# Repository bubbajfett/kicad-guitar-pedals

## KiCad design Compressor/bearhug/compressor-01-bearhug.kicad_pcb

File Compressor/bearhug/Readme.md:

# Bearhug

Guitar Pedal PCB based on Bearhug compressor.

Edit --- found a bug, and am now re-verifying this.   Consider this unverified, though it passes sound ok.

All registered trademarks are owned by their respective owners.

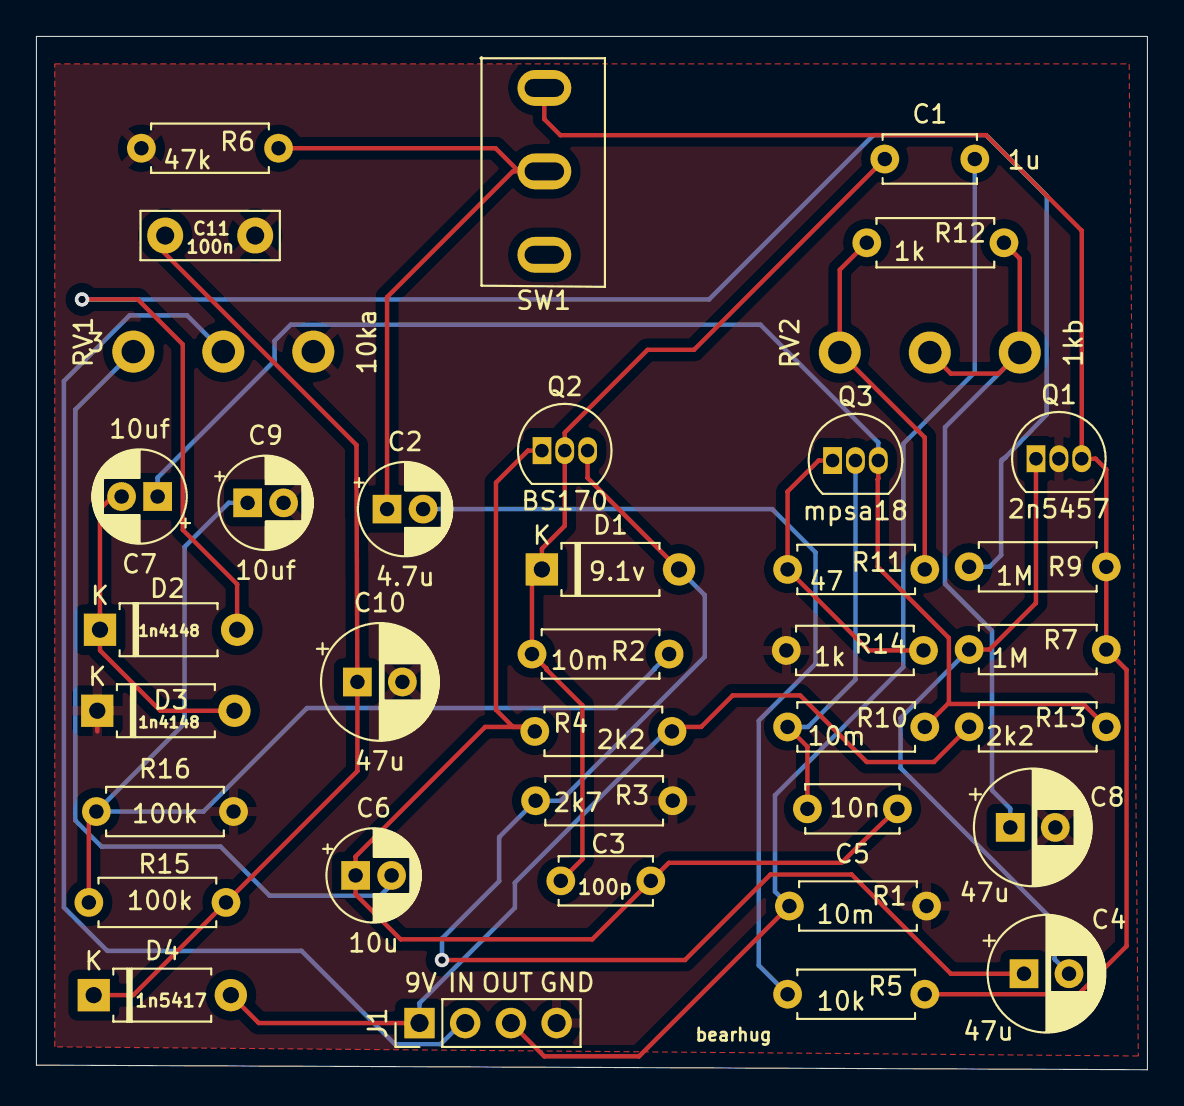
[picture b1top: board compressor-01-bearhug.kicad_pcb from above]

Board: 2 copper layers, 61.7 x 57.4 mm, 37 parts (0 on the bottom side), 21 nets.

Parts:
C1: 1u; C_Disc_D5.0mm_W2.5mm_P5.00mm
C2: 4.7u; CP_Radial_D5.0mm_P2.00mm
C3: 100p; C_Disc_D5.0mm_W2.5mm_P5.00mm
C4, C8, C10: 47u; CP_Radial_D6.3mm_P2.50mm
C5: 10n; C_Disc_D5.0mm_W2.5mm_P5.00mm
C6: 10u; CP_Radial_D5.0mm_P2.00mm
C7, C9: 10uf; CP_Radial_D5.0mm_P2.00mm
C11: 100n; C_Disc_D7.5mm_W2.5mm_P5.00mm
D1: 9.1v; D_A-405_P7.62mm_Horizontal
D2, D3: 1n4148; D_A-405_P7.62mm_Horizontal
D4: 1n5417; D_A-405_P7.62mm_Horizontal
J1: Conn_01x05; PinHeader_1x04_P2.54mm_Vertical
Q1: 2n5457; TO-92_Inline
Q2: BS170; TO-92_Inline
Q3: mpsa18; TO-92_Inline
R1, R2, R10: 10m; R_Axial_DIN0207_L6.3mm_D2.5mm_P7.62mm_Horizontal
R3: 2k7; R_Axial_DIN0207_L6.3mm_D2.5mm_P7.62mm_Horizontal
R4, R13: 2k2; R_Axial_DIN0207_L6.3mm_D2.5mm_P7.62mm_Horizontal
R5: 10k; R_Axial_DIN0207_L6.3mm_D2.5mm_P7.62mm_Horizontal
R6: 47k; R_Axial_DIN0207_L6.3mm_D2.5mm_P7.62mm_Horizontal
R7, R9: 1M; R_Axial_DIN0207_L6.3mm_D2.5mm_P7.62mm_Horizontal
R11: 47; R_Axial_DIN0207_L6.3mm_D2.5mm_P7.62mm_Horizontal
R12, R14: 1k; R_Axial_DIN0207_L6.3mm_D2.5mm_P7.62mm_Horizontal
R15, R16: 100k; R_Axial_DIN0207_L6.3mm_D2.5mm_P7.62mm_Horizontal
RV1: 10ka; Pot_Underside
RV2: 1kb; Pot_Underside
SW1: SW_SPST; SWITCH-M1-SPDT

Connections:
9v: D4.2 (A), J1.1, R4.1, R13.1
GND: C8.2, C9.2, C10.2, C11.2, D3.1 (K), J1.4, Q1.2 (S), R1.2, R3.2, R6.1, R14.2, R16.2, RV1.1
IN: C1.2, J1.3, R1.1
unnamed: C2.2, R5.1
unnamed: C6.2, RV1.3
unnamed: C8.1, R12.2, RV2.1, RV2.2
unnamed: C4.1, D1.2 (A), Q2.3 (S), R3.1
unnamed: C1.1, C3.1, D1.1 (K), Q2.2 (G), R2.1
unnamed: D2.2 (A), R9.2
unnamed: C7.2, D2.1 (K), D3.2 (A)
unnamed: C10.1, C11.1, D4.1 (K), R15.1
unnamed: C4.2, Q1.1 (D), R7.1
unnamed: Q1.3 (G), R5.2, R7.2, R9.1, SW1.1 (A)
unnamed: C3.2, C5.1, C6.1, Q2.1 (D), R4.2
unnamed: C5.2, Q3.2 (B), R10.1
unnamed: C7.1, Q3.3 (C), R10.2, R13.2
unnamed: Q3.1 (E), R11.1, R14.1
unnamed: R11.2, R12.1, RV2.3
unnamed: C2.1, R6.2, SW1.2 (B)
OUT: J1.2, RV1.2
VB: C9.1, R2.2, R15.2, R16.1

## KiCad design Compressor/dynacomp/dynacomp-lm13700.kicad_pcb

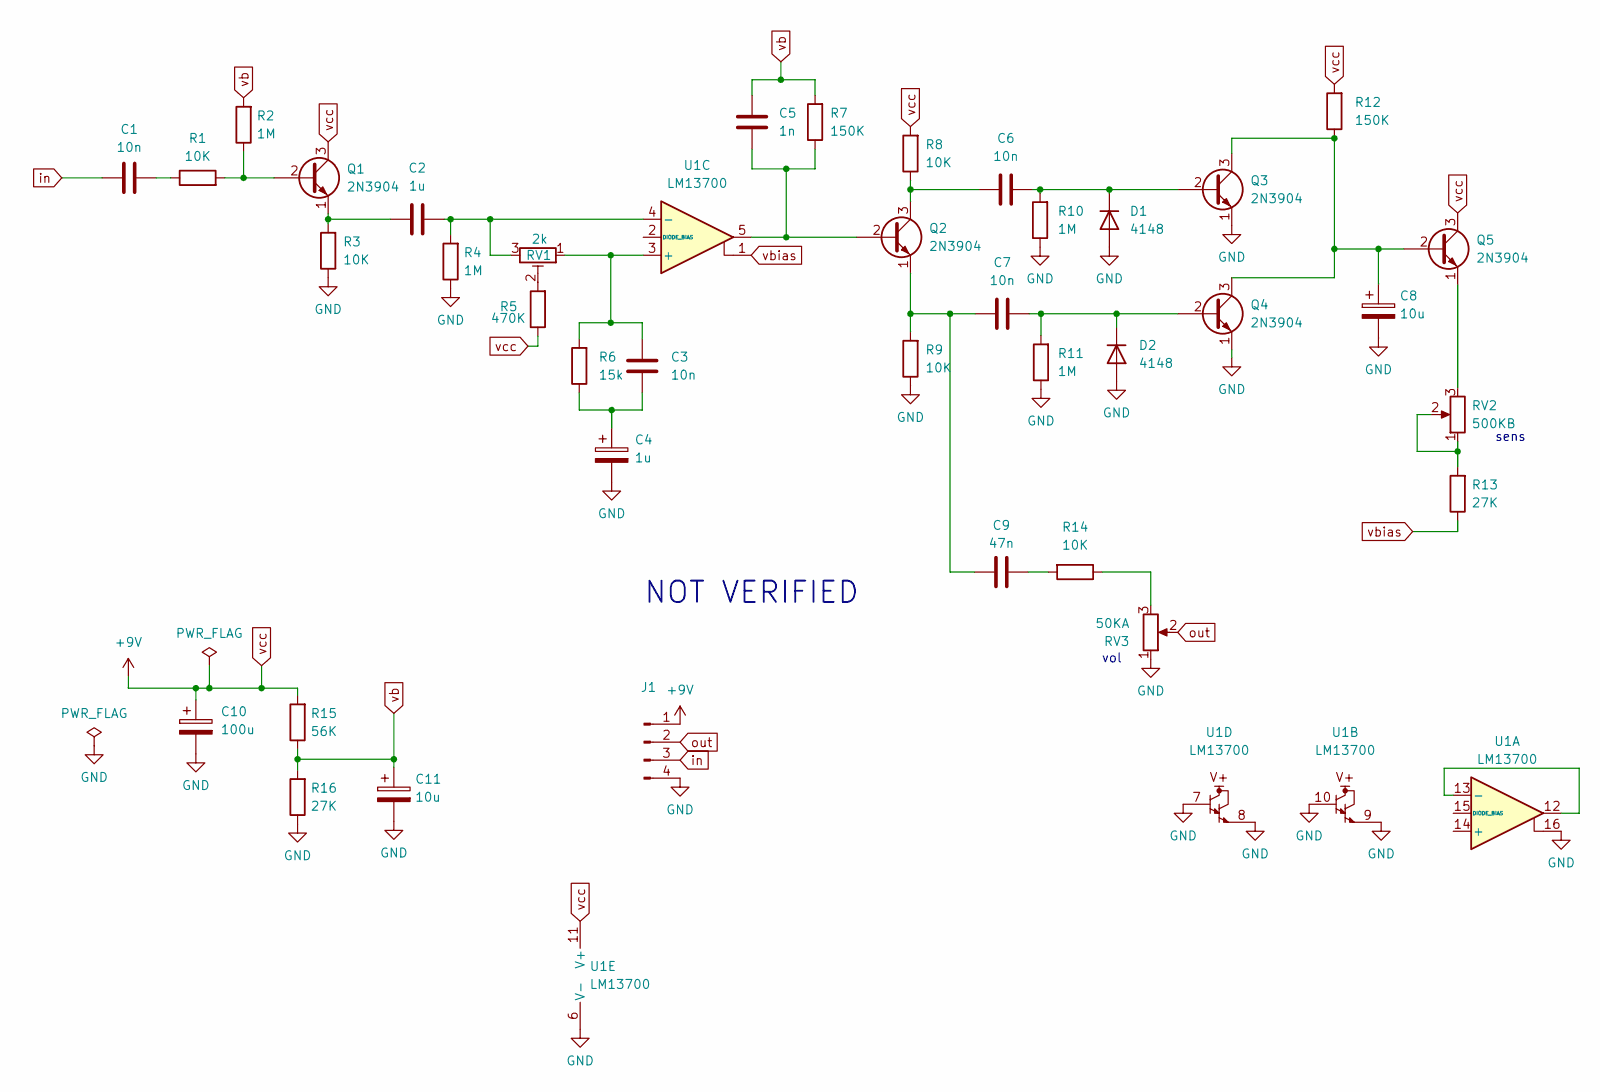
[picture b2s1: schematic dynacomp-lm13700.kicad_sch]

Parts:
C1, C3, C6, C7: 10n; C_Rect_L7.0mm_W2.0mm_P5.00mm
C2: 1u; C_Rect_L7.0mm_W3.5mm_P5.00mm
C4: 1u; CP_Radial_D5.0mm_P2.00mm
C5: 1n; C_Rect_L7.0mm_W2.0mm_P5.00mm
C8, C11: 10u; CP_Radial_D5.0mm_P2.00mm
C9: 47n; C_Rect_L7.0mm_W2.0mm_P5.00mm
C10: 100u; CP_Radial_D6.3mm_P2.50mm
D1, D2: 4148; D_DO-35_SOD27_P7.62mm_Horizontal
J1: Conn_01x04_Pin; PinHeader_1x04_P2.54mm_Vertical
Q1, Q2, Q3, Q4, Q5: 2N3904; TO-92_Inline
R1, R3, R8, R9, R14: 10K; R_Axial_DIN0207_L6.3mm_D2.5mm_P10.16mm_Horizontal
R2, R4, R10, R11: 1M; R_Axial_DIN0207_L6.3mm_D2.5mm_P10.16mm_Horizontal
R5: 470K; R_Axial_DIN0207_L6.3mm_D2.5mm_P10.16mm_Horizontal
R6: 15k; R_Axial_DIN0207_L6.3mm_D2.5mm_P10.16mm_Horizontal
R7, R12: 150K; R_Axial_DIN0207_L6.3mm_D2.5mm_P10.16mm_Horizontal
R13, R16: 27K; R_Axial_DIN0207_L6.3mm_D2.5mm_P10.16mm_Horizontal
R15: 56K; R_Axial_DIN0207_L6.3mm_D2.5mm_P10.16mm_Horizontal
RV1: 2k; Potentiometer_Runtron_RM-065_Vertical
RV2: 500KB; Pot_Underside
RV3: 50KA; Pot_Underside
U1: LM13700; DIP-16_W7.62mm

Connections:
GND: C4.2, C8.2, C10.2, C11.2, D1.2 (A), D2.2 (A), J1.4, Q3.1 (E), Q4.1 (E), R3.1, R4.1, R9.1, R10.1, R11.1, R16.1, RV3.1, U1.6 (V-), U1.7, U1.8, U1.9, U1.10, U1.16
unnamed: C1.2, R1.1
unnamed: C3.2, C4.1, R6.1
unnamed: C9.2, R14.2
unnamed: C6.2, D1.1 (K), Q3.2 (B), R10.2
unnamed: C7.2, D2.1 (K), Q4.2 (B), R11.2
unnamed: Q1.2 (B), R1.2, R2.1
unnamed: C2.1, Q1.1 (E), R3.2
unnamed: C5.2, Q2.2 (B), R7.1, U1.5
unnamed: C6.1, Q2.3 (C), R8.1
unnamed: C7.1, C9.1, Q2.1 (E), R9.2
unnamed: C8.1, Q3.3 (C), Q4.3 (C), Q5.2 (B), R12.1
unnamed: Q5.1 (E), RV2.3
unnamed: R5.2, RV1.2
unnamed: R13.2, RV2.1, RV2.2
unnamed: R14.1, RV3.3
unnamed: U1.12, U1.13 (-)
unnamed: C3.1, R6.2, RV1.1, U1.3 (+)
unnamed: C2.2, R4.2, RV1.3, U1.4 (-)
in: C1.1, J1.3
out: J1.2, RV3.2
vb: C5.1, C11.1, R2.2, R7.2, R15.1, R16.2
vbias: R13.1, U1.1
vcc: C10.1, J1.1, Q1.3 (C), Q5.3 (C), R5.1, R8.2, R12.2, R15.2, U1.11 (V+)

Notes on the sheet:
sens
vol
NOT VERIFIED

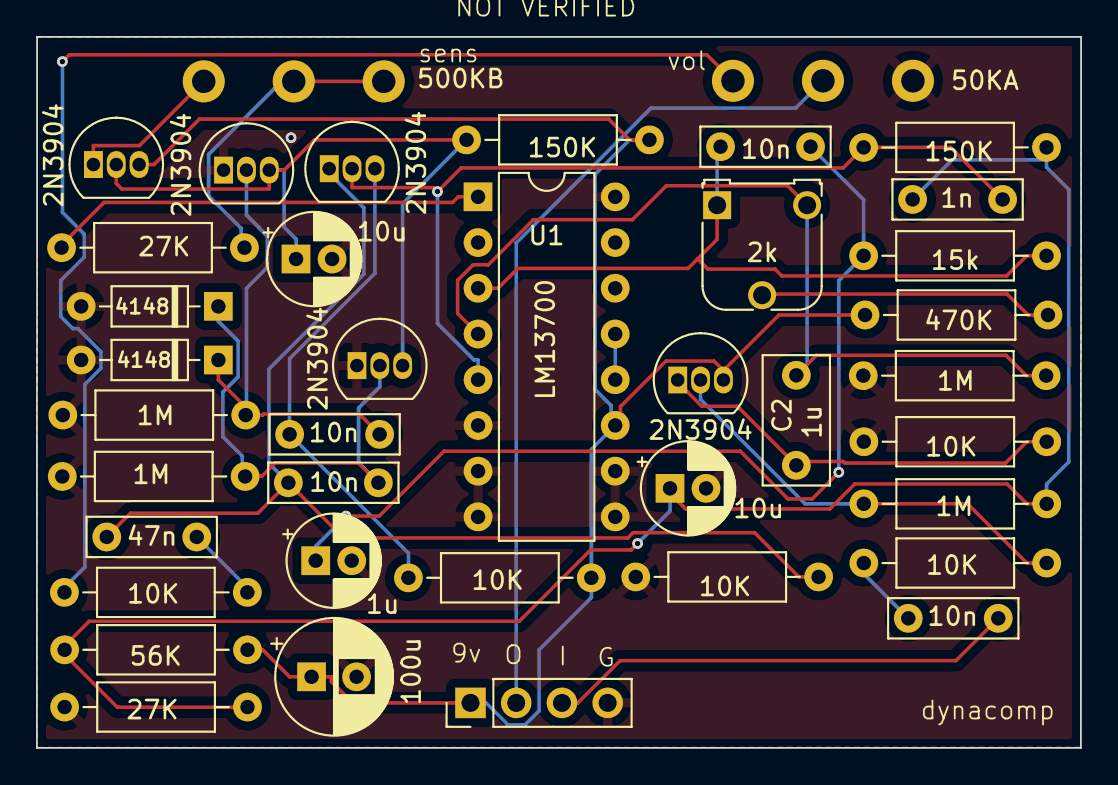
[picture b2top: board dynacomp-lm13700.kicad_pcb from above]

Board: 2 copper layers, 58.0 x 39.5 mm, 39 parts (0 on the bottom side), 24 nets.

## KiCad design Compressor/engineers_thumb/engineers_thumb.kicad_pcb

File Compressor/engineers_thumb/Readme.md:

# Engineers Thumb

This compressor uses OTA LM13700 IC for fairly subtle compression.  This
is verified.

Not sure this was a commercially sold compressor, or if it is a clone of
a commercially sold compressor.

All registered trademarks are owned by their respective owners.

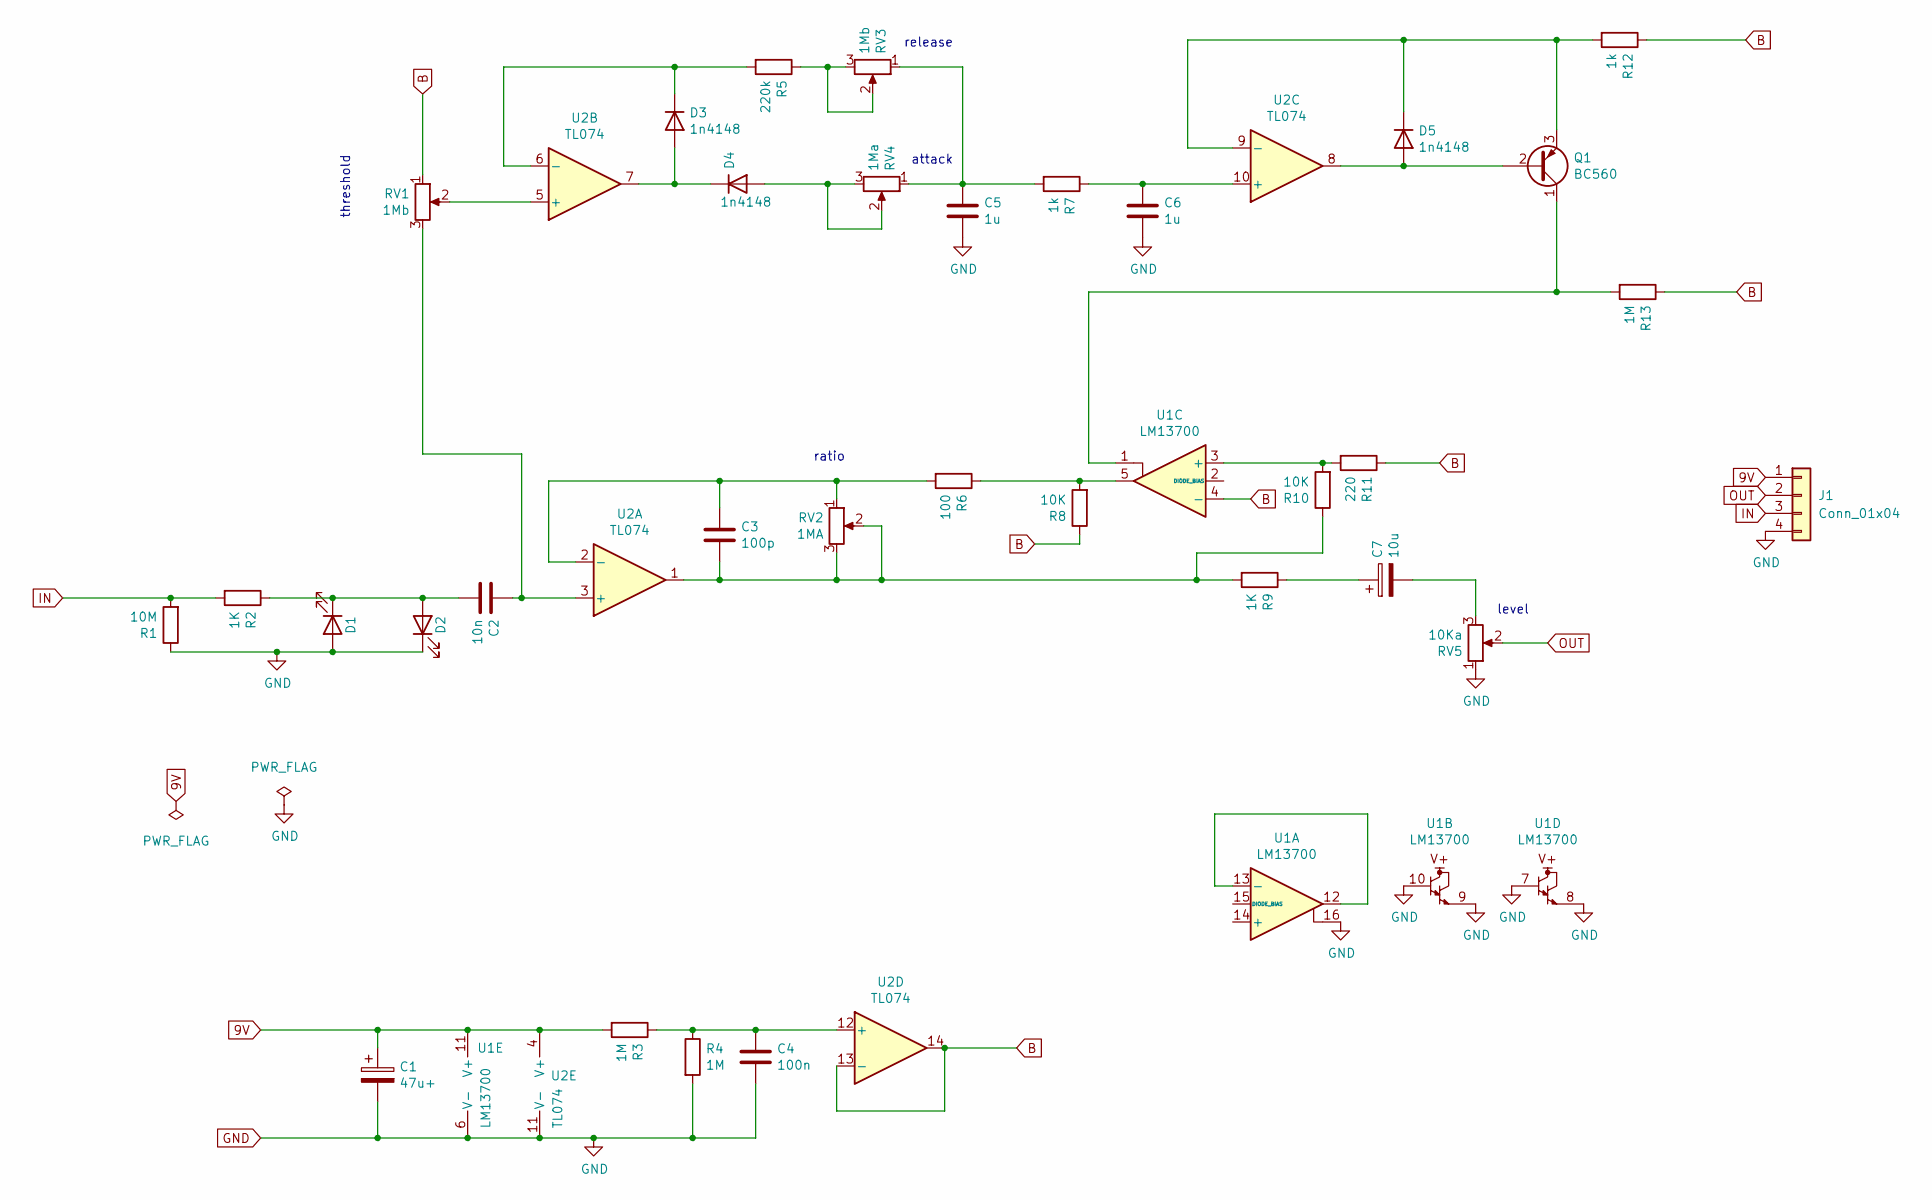
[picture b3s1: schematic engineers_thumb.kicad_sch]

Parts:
C1: 47u+; CP_Radial_D6.3mm_P2.50mm
C2: 10n; C_Rect_L7.0mm_W3.5mm_P5.00mm
C3: 100p; C_Disc_D5.1mm_W3.2mm_P5.00mm
C4: 100n; C_Rect_L7.0mm_W3.5mm_P5.00mm
C5, C6: 1u; C_Rect_L7.0mm_W3.5mm_P5.00mm
C7: 10u; CP_Radial_D5.0mm_P2.00mm
D1, D2: 3mm; LED_D3.0mm
D3, D4, D5: 1n4148; D_A-405_P7.62mm_Horizontal
J1: Conn_01x04; PinHeader_1x04_P2.54mm_Vertical
Q1: BC560; TO-92_Inline
R1: 10M; R_Axial_DIN0207_L6.3mm_D2.5mm_P10.16mm_Horizontal
R2, R9: 1K; R_Axial_DIN0207_L6.3mm_D2.5mm_P10.16mm_Horizontal
R3, R4, R13: 1M; R_Axial_DIN0207_L6.3mm_D2.5mm_P10.16mm_Horizontal
R5: 220k; R_Axial_DIN0207_L6.3mm_D2.5mm_P10.16mm_Horizontal
R6: 100; R_Axial_DIN0207_L6.3mm_D2.5mm_P10.16mm_Horizontal
R7, R12: 1k; R_Axial_DIN0207_L6.3mm_D2.5mm_P10.16mm_Horizontal
R8, R10: 10K; R_Axial_DIN0207_L6.3mm_D2.5mm_P10.16mm_Horizontal
R11: 220; R_Axial_DIN0207_L6.3mm_D2.5mm_P10.16mm_Horizontal
RV1, RV3: 1Mb; Potentiometer_Alps_RK09K_Single_Vertical
RV2: 1MA; Potentiometer_Alps_RK09K_Single_Vertical
RV4: 1Ma; Potentiometer_Alps_RK09K_Single_Vertical
RV5: 10Ka; Potentiometer_Alps_RK09K_Single_Vertical
U1: LM13700; DIP-16_W7.62mm_LongPads
U2: TL074; DIP-14_W7.62mm_LongPads

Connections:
9V: C1.1, J1.1, R3.2, U1.11 (V+), U2.4 (V+)
B: R8.1, R11.1, R12.1, R13.1, RV1.1, U1.4 (-), U2.13 (-), U2.14
GND: C1.2, C4.2, C5.2, C6.2, D1.2 (A), D2.1 (K), J1.4, R1.1, R4.2, RV5.1, U1.6 (V-), U1.7, U1.8, U1.9, U1.10, U1.16, U2.11 (V-)
IN: J1.3, R1.2, R2.2
unnamed: C3.2, R9.2, R10.1, RV2.2, RV2.3, U2.1
unnamed: C5.1, R7.2, RV3.1, RV4.1
unnamed: C7.1, R9.1
unnamed: C7.2, RV5.3
unnamed: C2.2, D1.1 (K), D2.2 (A), R2.1
unnamed: D3.2 (A), D4.1 (K), U2.7
unnamed: D3.1 (K), R5.2, U2.6 (-)
unnamed: D4.2 (A), RV4.2, RV4.3
unnamed: D5.2 (A), Q1.2 (B), U2.8
unnamed: D5.1 (K), Q1.3 (E), R12.2, U2.9 (-)
unnamed: Q1.1 (C), R13.2, U1.1
unnamed: R5.1, RV3.2, RV3.3
unnamed: R6.1, R8.2, U1.5
unnamed: U1.12, U1.13 (-)
unnamed: R10.2, R11.2, U1.3 (+)
unnamed: C2.1, RV1.3, U2.3 (+)
unnamed: C3.1, R6.2, RV2.1, U2.2 (-)
unnamed: RV1.2, U2.5 (+)
unnamed: C6.1, R7.1, U2.10 (+)
unnamed: C4.1, R3.1, R4.1, U2.12 (+)
OUT: J1.2, RV5.2

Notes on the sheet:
attack
ratio
level
threshold
release

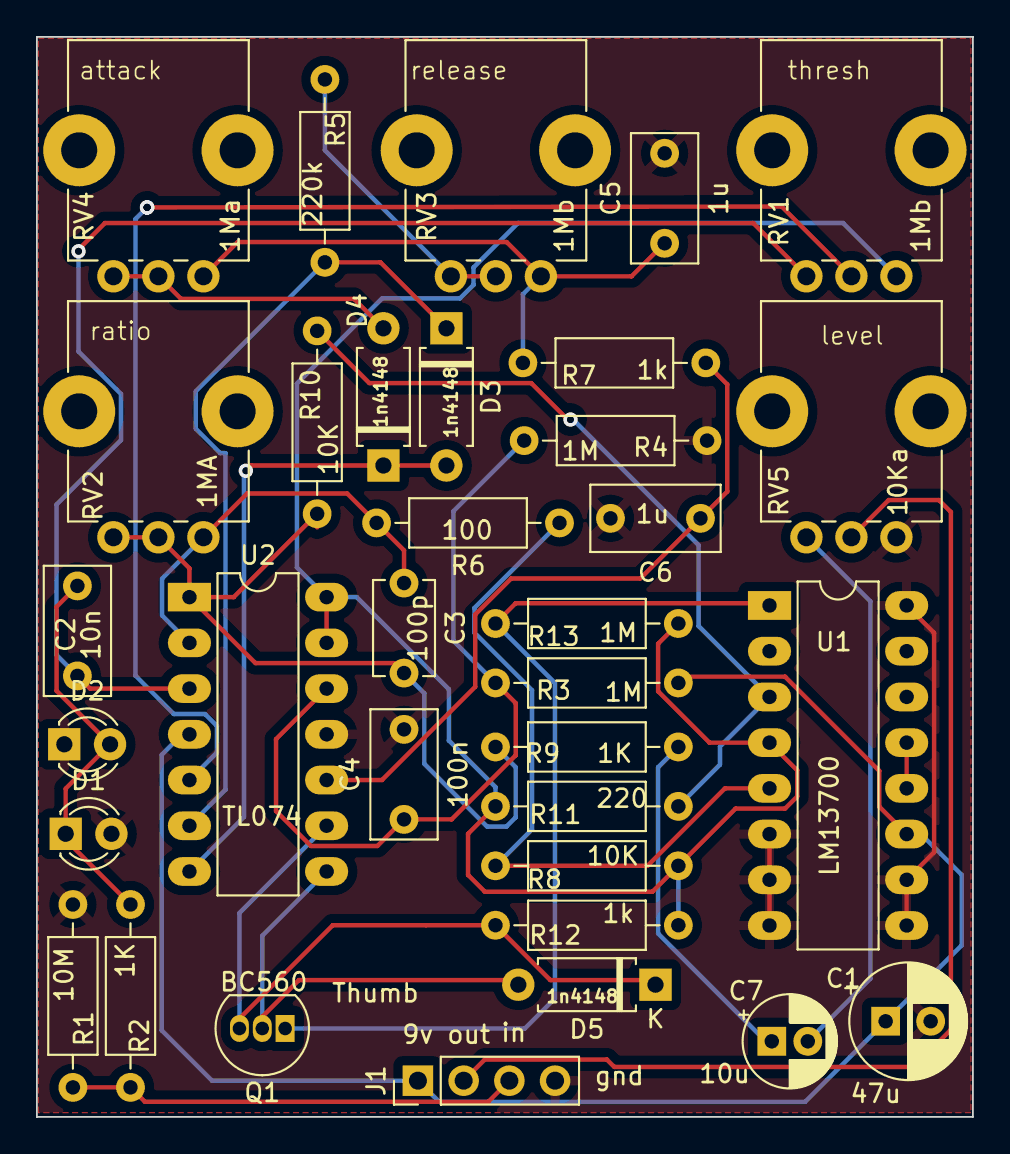
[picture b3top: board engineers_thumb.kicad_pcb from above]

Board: 2 copper layers, 52.0 x 60.0 mm, 34 parts (0 on the bottom side), 25 nets.

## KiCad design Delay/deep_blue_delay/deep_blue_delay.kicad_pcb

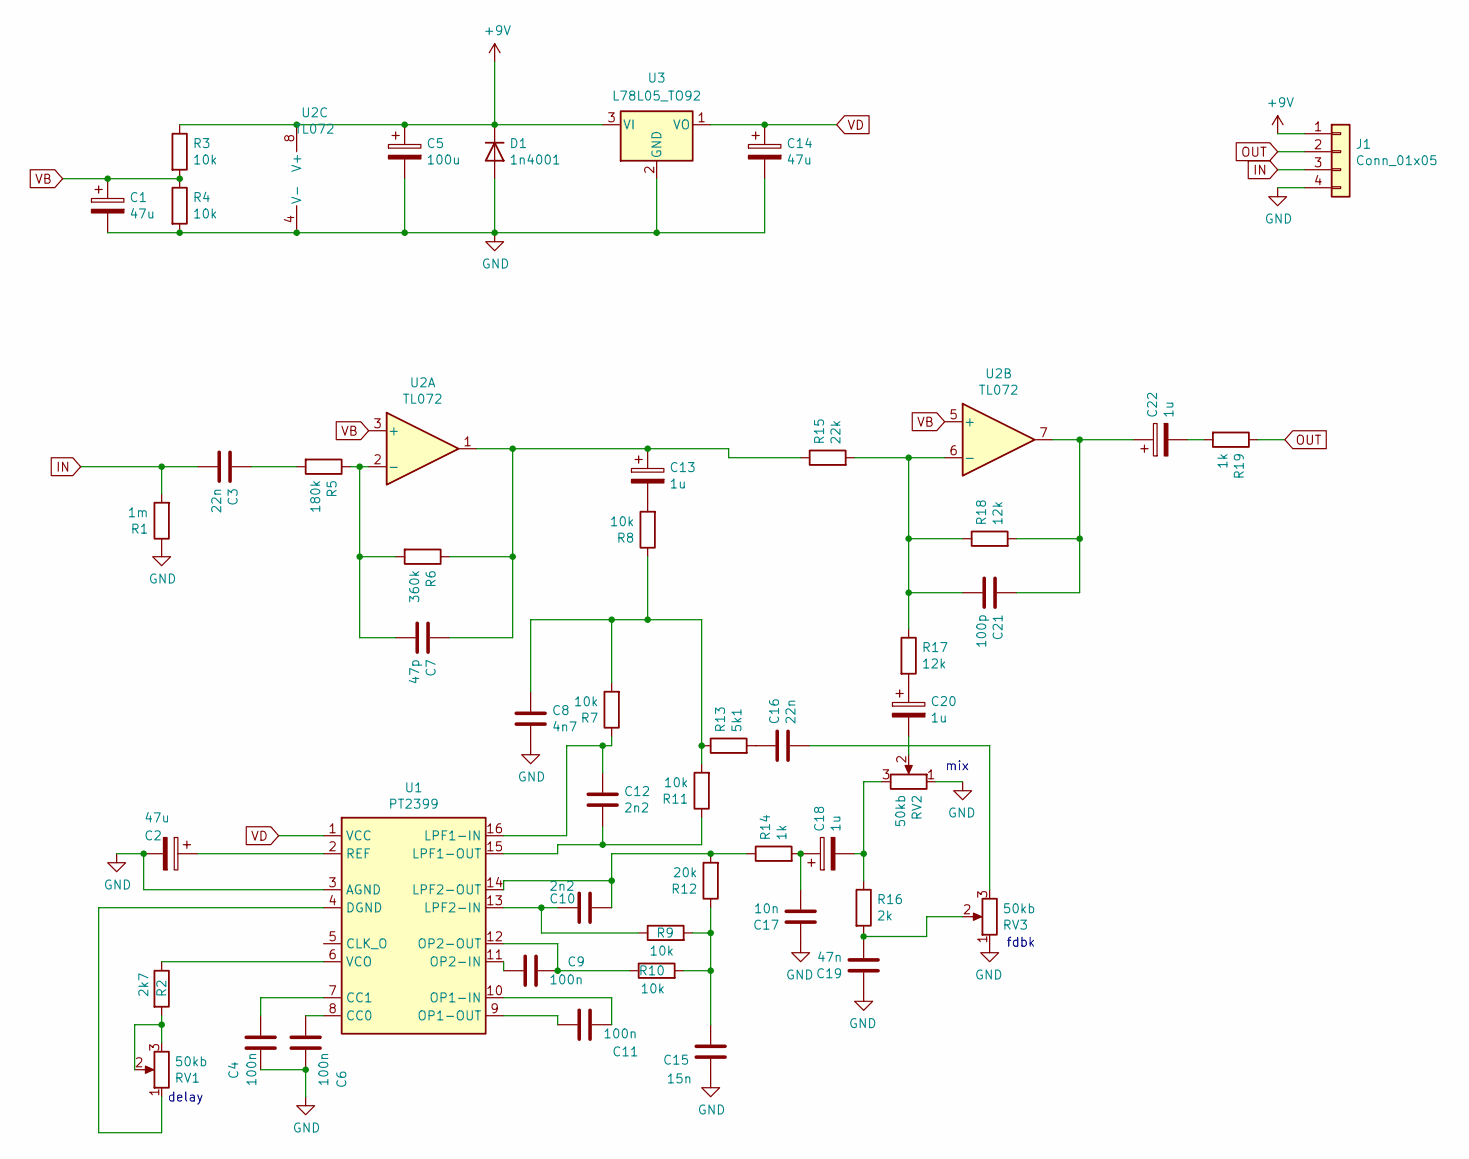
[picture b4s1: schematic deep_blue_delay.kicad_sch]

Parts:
C1, C2, C14: 47u; CP_Radial_D5.0mm_P2.00mm
C3, C16: 22n; C_Rect_L7.0mm_W3.5mm_P5.00mm
C4, C6, C9, C11: 100n; C_Disc_D5.0mm_W2.5mm_P5.00mm
C5: 100u; CP_Radial_D6.3mm_P2.50mm
C7: 47p; C_Disc_D5.1mm_W3.2mm_P5.00mm
C8: 4n7; C_Rect_L7.0mm_W3.5mm_P5.00mm
C10: 2n2; C_Disc_D5.0mm_W2.5mm_P5.00mm
C12: 2n2; C_Rect_L7.0mm_W3.5mm_P5.00mm
C13: 1u; CP_Radial_D6.3mm_P2.50mm
C15: 15n; C_Disc_D5.0mm_W2.5mm_P5.00mm
C17: 10n; C_Rect_L7.0mm_W3.5mm_P5.00mm
C18, C20, C22: 1u; CP_Radial_D5.0mm_P2.00mm
C19: 47n; C_Rect_L7.0mm_W3.5mm_P5.00mm
C21: 100p; C_Disc_D5.1mm_W3.2mm_P5.00mm
D1: 1n4001; D_A-405_P7.62mm_Horizontal
J1: Conn_01x05; PinHeader_1x04_P2.54mm_Vertical
R1: 1m; R_Axial_DIN0207_L6.3mm_D2.5mm_P10.16mm_Horizontal
R2: 2k7; R_Axial_DIN0207_L6.3mm_D2.5mm_P10.16mm_Horizontal
R3, R4, R7, R8, R9, R10, R11: 10k; R_Axial_DIN0207_L6.3mm_D2.5mm_P10.16mm_Horizontal
R5: 180k; R_Axial_DIN0207_L6.3mm_D2.5mm_P10.16mm_Horizontal
R6: 360k; R_Axial_DIN0207_L6.3mm_D2.5mm_P10.16mm_Horizontal
R12: 20k; R_Axial_DIN0207_L6.3mm_D2.5mm_P10.16mm_Horizontal
R13: 5k1; R_Axial_DIN0207_L6.3mm_D2.5mm_P10.16mm_Horizontal
R14, R19: 1k; R_Axial_DIN0207_L6.3mm_D2.5mm_P10.16mm_Horizontal
R15: 22k; R_Axial_DIN0207_L6.3mm_D2.5mm_P10.16mm_Horizontal
R16: 2k; R_Axial_DIN0207_L6.3mm_D2.5mm_P10.16mm_Horizontal
R17, R18: 12k; R_Axial_DIN0207_L6.3mm_D2.5mm_P10.16mm_Horizontal
RV1, RV2, RV3: 50kb; SolderWirePad_1x03_P4.445mm_Drill1.5mm
U1: PT2399; DIP-16_W7.62mm
U2: TL072; DIP-8_W7.62mm
U3: L78L05_TO92; TO-92_Inline

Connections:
+9V: C5.1, D1.1 (K), J1.1, R3.1, U2.8 (V+), U3.3 (VI)
GND: C1.2, C2.2, C4.1, C5.2, C6.1, C8.2, C14.2, C15.1, C17.1, C19.1, D1.2 (A), J1.4, R1.1, R4.2, RV2.1, RV3.1, U1.3 (AGND), U2.4 (V-), U3.2 (GND)
IN: C3.2, J1.3, R1.2
unnamed: C2.1, U1.2 (REF)
unnamed: C3.1, R5.2
unnamed: C4.2, U1.7 (CC1)
unnamed: C6.2, U1.8 (CC0)
unnamed: C7.2, R5.1, R6.2, U2.2 (-)
unnamed: C8.1, R7.2, R8.1, R11.2, R13.1
unnamed: C9.1, R10.1, U1.12 (OP2-OUT)
unnamed: C9.2, U1.11 (OP2-IN)
unnamed: C10.1, R12.2, R14.1, U1.14 (LPF2-OUT)
unnamed: C10.2, R9.1, U1.13 (LPF2-IN)
unnamed: C11.1, U1.10 (OP1-IN)
unnamed: C11.2, U1.9 (OP1-OUT)
unnamed: C12.1, R7.1, U1.16 (LPF1-IN)
unnamed: C12.2, R11.1, U1.15 (LPF1-OUT)
unnamed: C7.1, C13.1, R6.1, R15.1, U2.1
unnamed: C13.2, R8.2
unnamed: C15.2, R9.2, R10.2, R12.1
unnamed: C16.1, R13.2
unnamed: C16.2, RV3.3
unnamed: C17.2, C18.1, R14.2
unnamed: C18.2, R16.1, RV2.3
unnamed: C19.2, R16.2, RV3.2
unnamed: C20.1, R17.2
unnamed: C20.2, RV2.2
unnamed: C21.1, C22.1, R18.2, U2.7
unnamed: C21.2, R15.2, R17.1, R18.1, U2.6 (-)
unnamed: C22.2, R19.2
unnamed: R2.1, U1.6 (VCO)
unnamed: R2.2, RV1.2, RV1.3
unnamed: RV1.1, U1.4 (DGND)
OUT: J1.2, R19.1
VB: C1.1, R3.2, R4.1, U2.3 (+), U2.5 (+)
VD: C14.1, U1.1 (VCC), U3.1 (VO)

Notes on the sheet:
mix
delay
fdbk

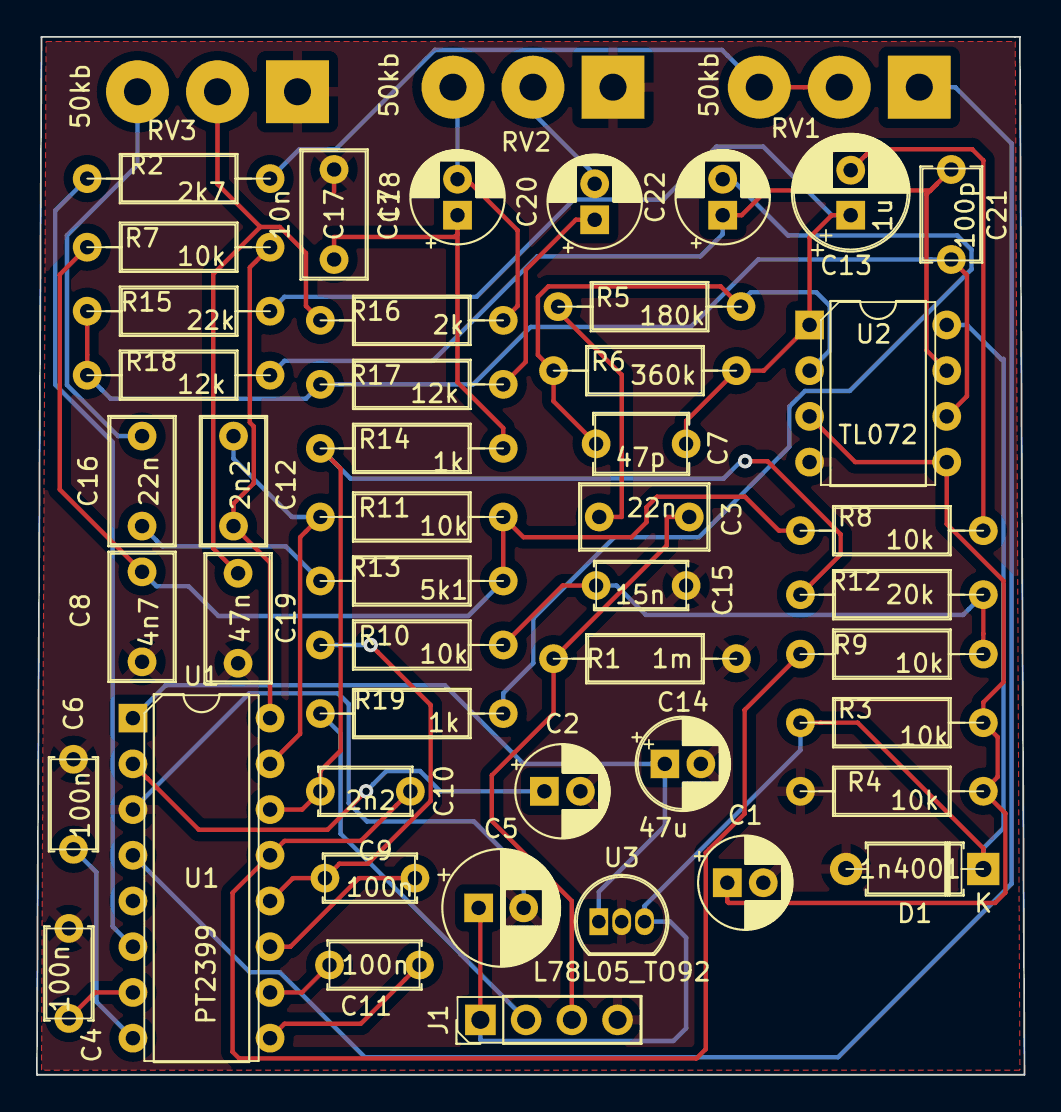
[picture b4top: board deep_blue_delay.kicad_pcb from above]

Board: 2 copper layers, 54.9 x 57.7 mm, 49 parts (0 on the bottom side), 36 nets.

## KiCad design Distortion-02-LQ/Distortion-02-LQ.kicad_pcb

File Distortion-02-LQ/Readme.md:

Distortion pedal based on the Lizard Queen

Schematic 

pcb layout

All trademarks belong to their respective owners.

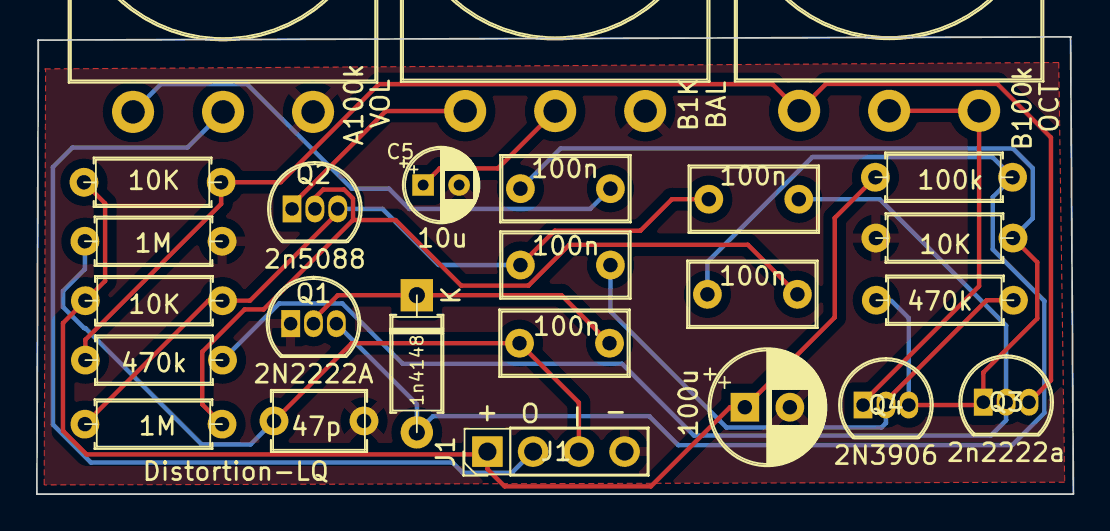
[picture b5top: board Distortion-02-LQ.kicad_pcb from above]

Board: 2 copper layers, 57.6 x 25.4 mm, 25 parts (0 on the bottom side), 16 nets.

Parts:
C1: 47p; C_Disc_D5.1mm_W3.2mm_P5.00mm
C2: 100u; CP_Radial_D6.3mm_P2.50mm
C3, C4, C6, C7, C8: 100n; C_Rect_L7.0mm_W3.5mm_P5.00mm
C5: 10u; CP_Radial_D4.0mm_P2.00mm
D1: 1n4148; D_A-405_P7.62mm_Horizontal
J1: Conn_01x04; PinHeader_1x04_P2.54mm_Vertical
Q1: 2N2222A; TO-92_Inline
Q2: 2n5088; TO-92_Inline
Q3: 2n2222a; TO-92_Inline
Q4: 2N3906; TO-92_Inline
R1, R4: 1M; R_Axial_DIN0207_L6.3mm_D2.5mm_P7.62mm_Horizontal
R2: 100k; R_Axial_DIN0207_L6.3mm_D2.5mm_P7.62mm_Horizontal
R3, R5, R7: 10K; R_Axial_DIN0207_L6.3mm_D2.5mm_P7.62mm_Horizontal
R6, R8: 470k; R_Axial_DIN0207_L6.3mm_D2.5mm_P7.62mm_Horizontal
RV1: B1K; Potentiometer_Omeg_PC16BU_Vertical
RV2: B100k; Potentiometer_Omeg_PC16BU_Vertical
RV3: A100k; Potentiometer_Omeg_PC16BU_Vertical

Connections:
+9V: C2.1, J1.1, R2.1, R3.1, R5.1
GND: C1.2, C2.2, C5.2, J1.4, Q1.1 (E), R1.2, R7.2, RV1.1, RV3.1
IN: C1.1, C3.1, J1.3, R1.1
unnamed: C3.2, D1.1 (K), Q1.2 (B)
unnamed: C4.1, D1.2 (A), Q1.3 (C), R2.2
unnamed: C4.2, Q2.2 (B), R4.2
unnamed: C5.1, RV1.2
unnamed: C6.1, C7.1, Q2.3 (C), R3.2, R4.1
unnamed: C6.2, Q3.2 (B), R6.2
unnamed: C7.2, Q4.2 (B), R8.2
unnamed: C8.1, Q3.1 (E), Q4.3 (C), R7.1, R8.1
unnamed: C8.2, RV3.3
unnamed: Q2.1 (E), RV1.3
unnamed: Q3.3 (C), R5.2, R6.1, RV2.3
unnamed: Q4.1 (E), RV2.1, RV2.2
out: J1.2, RV3.2

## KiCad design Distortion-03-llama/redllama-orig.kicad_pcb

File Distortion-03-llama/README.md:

Distortion pedal, loosely based on the red llama pedal.

This is unverified.

All trademarks belong to their respective trademark owners.

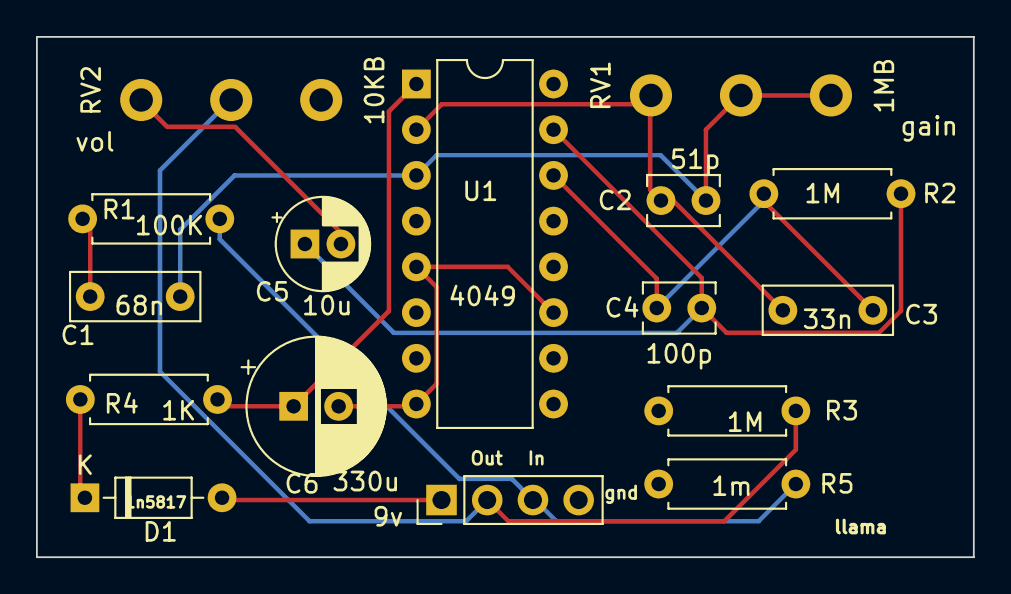
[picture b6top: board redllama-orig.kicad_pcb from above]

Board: 2 copper layers, 52.1 x 28.9 mm, 16 parts (0 on the bottom side), 12 nets.

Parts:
C1: 68n; C_Rect_L7.0mm_W2.5mm_P5.00mm
C2: 51p; C_Disc_D3.8mm_W2.6mm_P2.50mm
C3: 33n; C_Rect_L7.0mm_W2.5mm_P5.00mm
C4: 100p; C_Disc_D3.8mm_W2.6mm_P2.50mm
C5: 10u; CP_Radial_D5.0mm_P2.00mm
C6: 330u; CP_Radial_D7.5mm_P2.50mm
D1: 1n5817; D_DO-35_SOD27_P7.62mm_Horizontal
J1: Conn_01x04_Female; PinHeader_1x04_P2.54mm_Vertical
R1: 100K; R_Axial_DIN0207_L6.3mm_D2.5mm_P7.62mm_Horizontal
R2, R3: 1M; R_Axial_DIN0207_L6.3mm_D2.5mm_P7.62mm_Horizontal
R4: 1K; R_Axial_DIN0207_L6.3mm_D2.5mm_P7.62mm_Horizontal
R5: 1m; R_Axial_DIN0207_L6.3mm_D2.5mm_P7.62mm_Horizontal
RV1: 1MB; Pot_Underside
RV2: 10KB; Pot_Underside
U1: 4049; DIP-16_W7.62mm

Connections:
9v: D1.2 (A), J1.1
GND: C6.2, J1.4, R3.1, R5.1, RV2.1, U1.5, U1.7, U1.8 (VSS), U1.9, U1.11
IN: J1.3, R1.1, R5.2
unnamed: C1.1, R1.2
unnamed: C1.2, C2.1, RV1.1, U1.3
unnamed: C2.2, C3.1, RV1.2, RV1.3, U1.2
unnamed: C3.2, C4.1, R2.1, U1.14
unnamed: C4.2, C5.1, R2.2, U1.15
unnamed: C5.2, RV2.3
unnamed: D1.1 (K), R4.1
unnamed: C6.1, R4.2, U1.1 (VCC)
out: J1.2, R3.2, RV2.2

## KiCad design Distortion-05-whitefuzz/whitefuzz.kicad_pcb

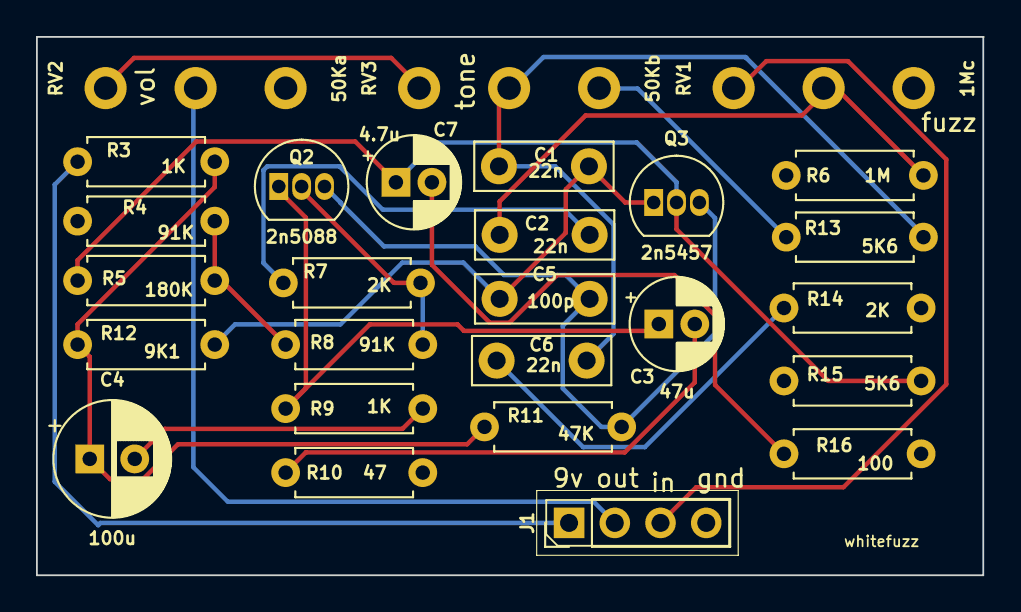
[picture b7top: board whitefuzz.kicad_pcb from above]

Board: 2 copper layers, 52.6 x 29.9 mm, 27 parts (0 on the bottom side), 19 nets.

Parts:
C1, C2, C6: 22n; C_Disc_D7.5mm_W2.5mm_P5.00mm
C3: 47u; CP_Radial_D5.0mm_P2.00mm
C4: 100u; CP_Radial_D6.3mm_P2.50mm
C5: 100p; C_Disc_D7.5mm_W2.5mm_P5.00mm
C7: 4.7u; CP_Radial_D5.0mm_P2.00mm
J1: Conn_01x04_Female; PinHeader_1x04_P2.54mm_Vertical
Q2: 2n5088; TO-92_Inline
Q3: 2n5457; TO-92_Inline
R3, R9: 1K; R_Axial_DIN0207_L6.3mm_D2.5mm_P7.62mm_Horizontal
R4, R8: 91K; R_Axial_DIN0207_L6.3mm_D2.5mm_P7.62mm_Horizontal
R5: 180K; R_Axial_DIN0207_L6.3mm_D2.5mm_P7.62mm_Horizontal
R6: 1M; R_Axial_DIN0207_L6.3mm_D2.5mm_P7.62mm_Horizontal
R7, R14: 2K; R_Axial_DIN0207_L6.3mm_D2.5mm_P7.62mm_Horizontal
R10: 47; R_Axial_DIN0207_L6.3mm_D2.5mm_P7.62mm_Horizontal
R11: 47K; R_Axial_DIN0207_L6.3mm_D2.5mm_P7.62mm_Horizontal
R12: 9K1; R_Axial_DIN0207_L6.3mm_D2.5mm_P7.62mm_Horizontal
R13, R15: 5K6; R_Axial_DIN0207_L6.3mm_D2.5mm_P7.62mm_Horizontal
R16: 100; R_Axial_DIN0207_L6.3mm_D2.5mm_P7.62mm_Horizontal
RV1: 1Mc; Pot_Underside
RV2: 50Ka; Pot_Underside
RV3: 50Kb; Pot_Underside

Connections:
9V: J1.1, R3.1
GND: C4.2, J1.4, R4.1, R6.1, R9.2, R10.2, R14.2, R15.1, R16.2, RV2.1
IN: J1.3, RV1.3
unnamed: C1.1, C6.2, R13.2, RV3.2
unnamed: C2.1, R6.2, RV1.2
unnamed: C2.2, R7.1
unnamed: C3.2, R10.1
unnamed: C4.1, R3.2, R11.1, R12.1
unnamed: C6.1, R14.1
unnamed: C7.2, R16.1
unnamed: Q2.2 (B), R7.2, R8.2
unnamed: C5.2, Q2.3 (C), Q3.3 (G), R11.2
unnamed: C3.1, Q2.1 (E), R9.1
unnamed: C1.2, C5.1, Q3.1 (D), R12.2
unnamed: C7.1, Q3.2 (S), R5.1, R15.2
unnamed: R4.2, R5.2, R8.1
unnamed: R13.1, RV3.1
unnamed: RV2.3, RV3.3
OUT: J1.2, RV2.2
